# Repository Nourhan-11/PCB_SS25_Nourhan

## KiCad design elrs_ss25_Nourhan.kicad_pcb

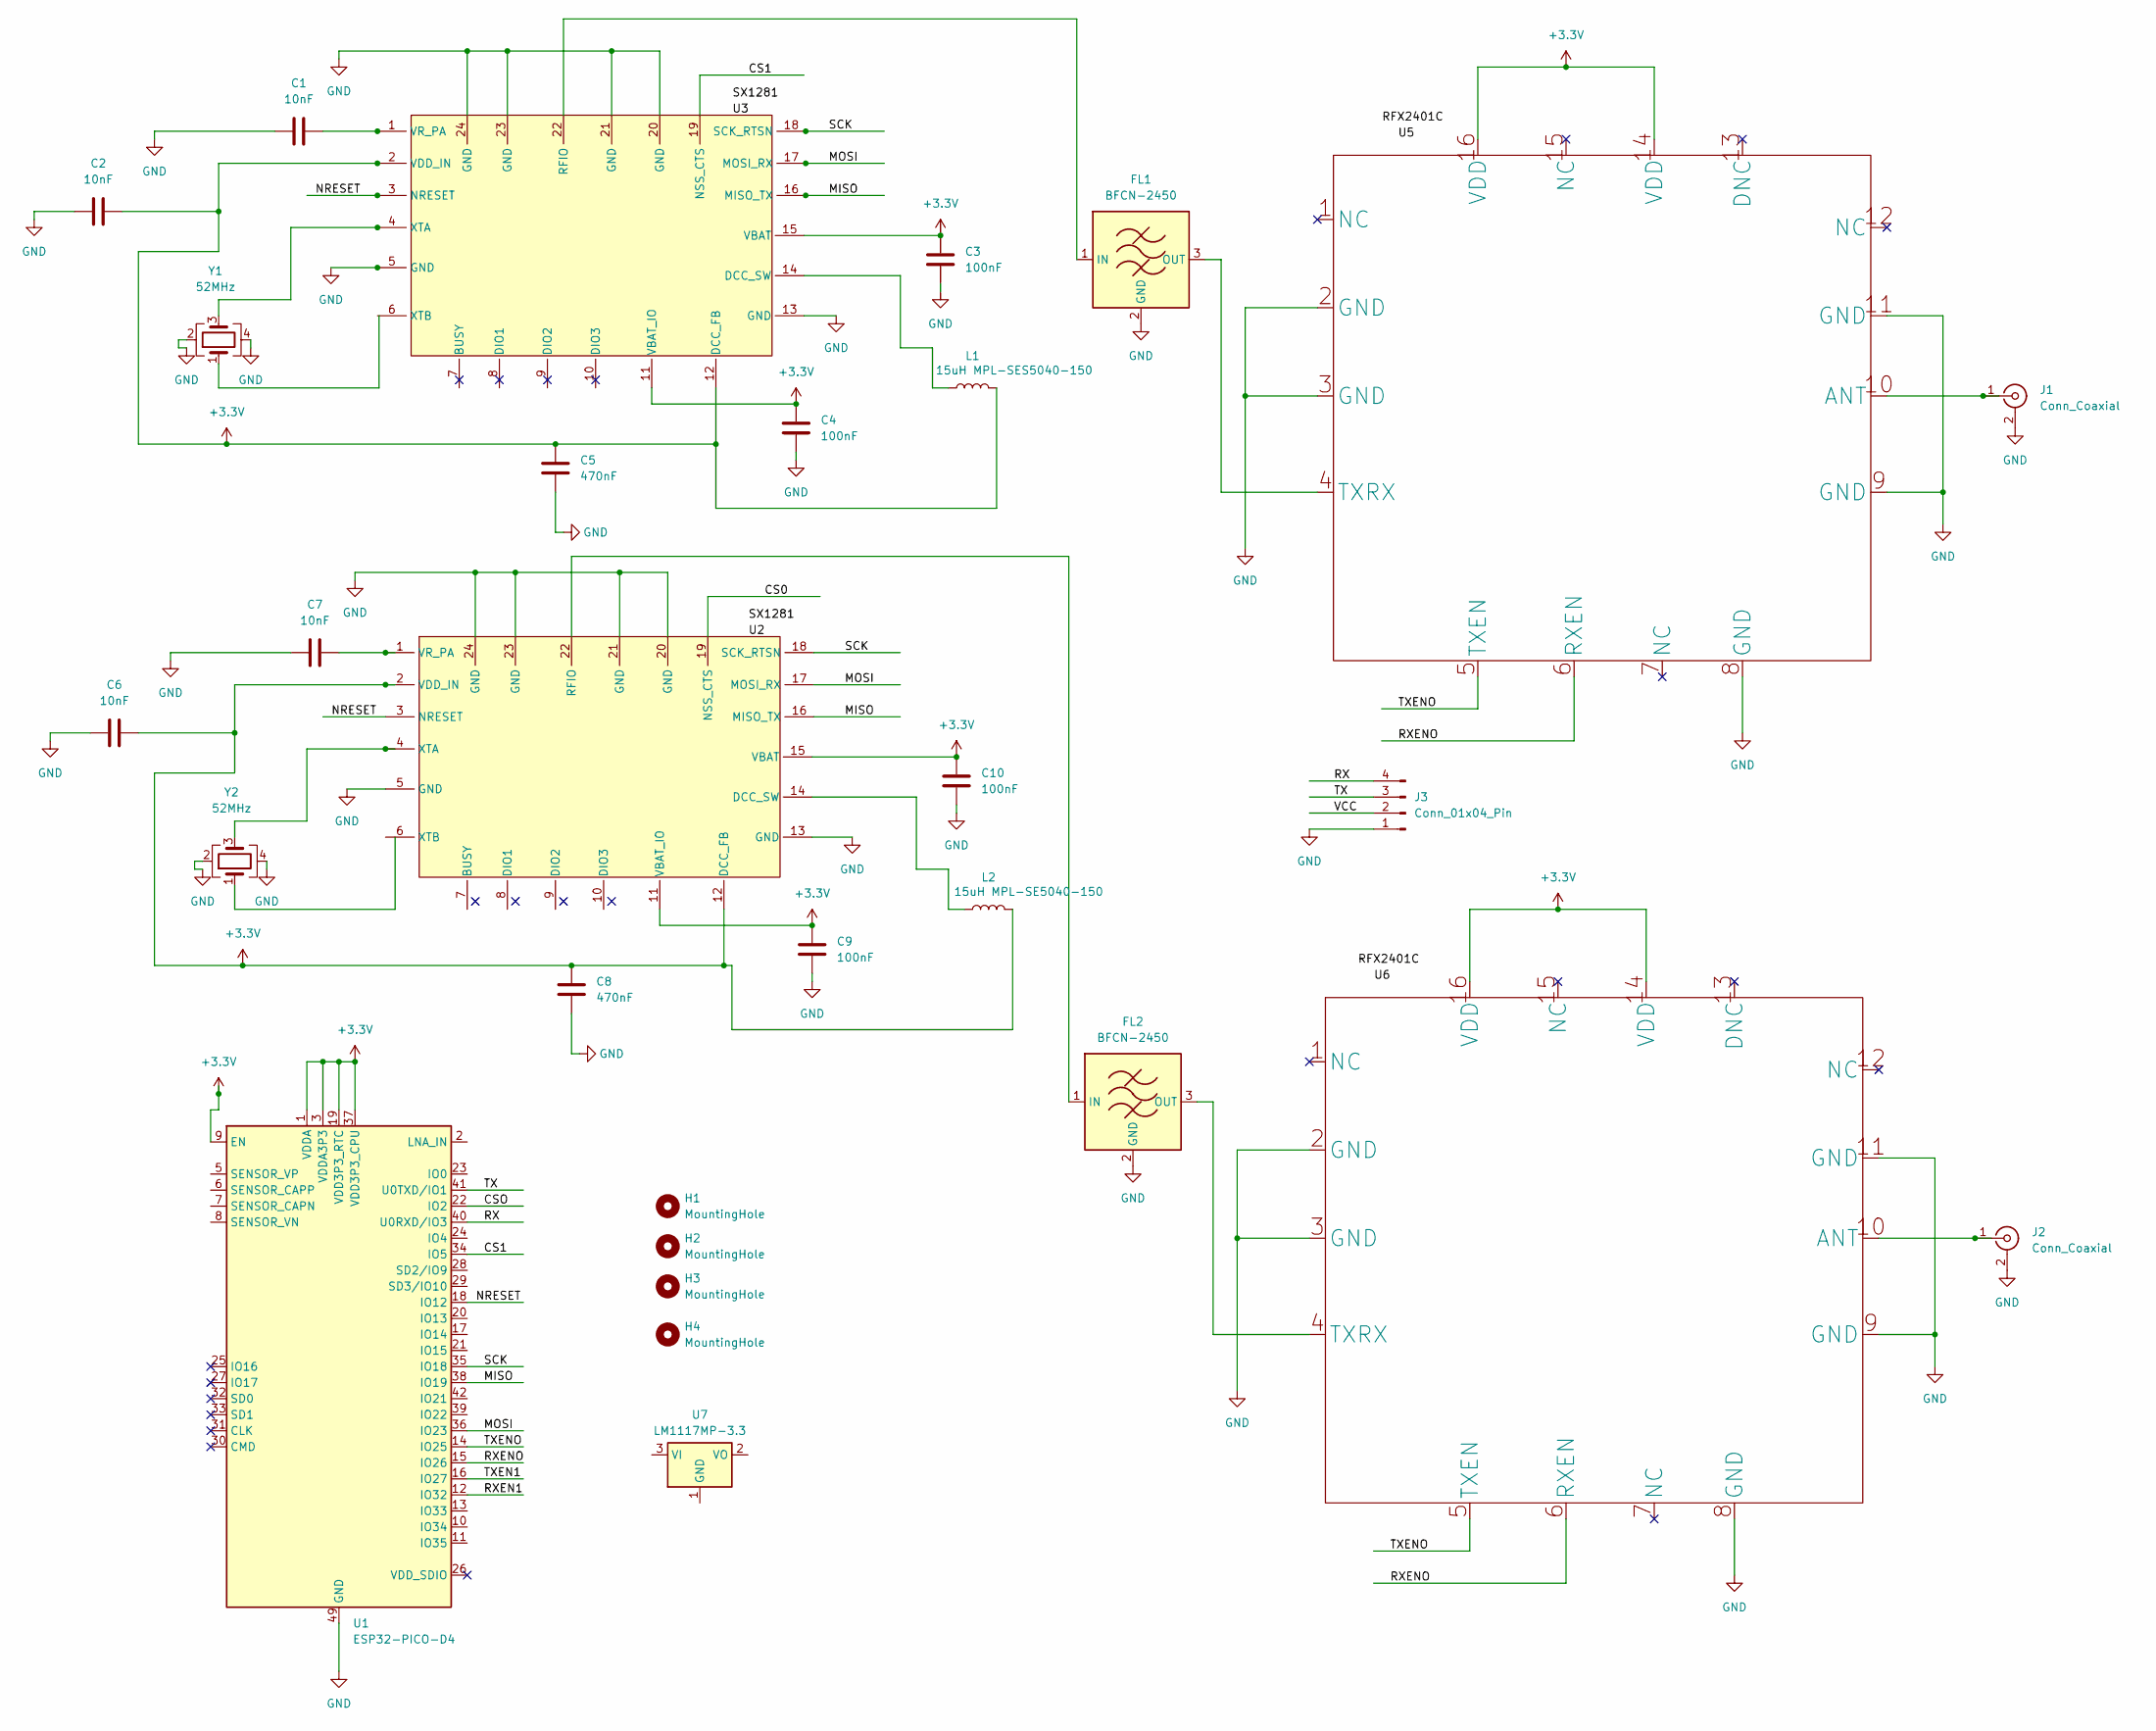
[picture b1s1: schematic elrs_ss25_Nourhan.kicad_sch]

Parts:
C1, C2, C6, C7: 10nF; C_0603_1608Metric_Pad1.08x0.95mm_HandSolder
C3, C4, C9, C10: 100nF; C_0603_1608Metric_Pad1.08x0.95mm_HandSolder
C5, C8: 470nF; C_0603_1608Metric_Pad1.08x0.95mm_HandSolder
FL1, FL2: BFCN-2450; Filter_Mini-Circuits_FV1206-4
H1, H2, H3, H4: MountingHole; MountingHole_3.2mm_M3
J1, J2: Conn_Coaxial; U.FL_Molex_MCRF_73412-0110_Vertical
J3: Conn_01x04_Pin; JST_GH_SM04B-GHS-TB_1x04-1MP_P1.25mm_Horizontal
L1: 15uH MPL-SES5040-150; L_APV_ANR5045
L2: 15uH MPL-SE5040-150; L_APV_ANR5045
U1: ESP32-PICO-D4; QFN-48-1EP_7x7mm_P0.5mm_EP5.3x5.3mm
U2, U3: QFN-24-1EP_4x4mm_P0.5mm_EP2.7x2.7mm
U4, U6: QFN-16-1EP_3x3mm_P0.5mm_EP1.75x1.75mm
U7: LM1117MP-3.3; SOT-223-3_TabPin2
Y1, Y2: 52MHz

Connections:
+3.3V: C2.2, C3.2, C4.2, C5.1, C6.2, C8.1, C9.2, C10.2, L1.2, L2.2, U1.1 (VDDA), U1.3 (VDDA3P3), U1.4 (VDDA3P3), U1.9 (EN), U1.19 (VDD3P3_RTC), U1.37 (VDD3P3_CPU), U1.43 (VDDA), U1.46 (VDDA), U2.2 (VDD_IN), U2.11 (VBAT_IO), U2.12 (DCC_FB), U2.15 (VBAT), U3.2 (VDD_IN), U3.11 (VBAT_IO), U3.12 (DCC_FB), U3.15 (VBAT), U4.14 (VDD), U4.16 (VDD), U6.14 (VDD), U6.16 (VDD); also elsewhere on the board
/CS0: U3.19 (NSS_CTS)
/CS1: U1.34 (IO5), U2.19 (NSS_CTS)
/CSO: U1.22 (IO2)
/MISO: U1.38 (IO19), U2.16 (MISO_TX), U3.16 (MISO_TX)
/MOSI: U1.36 (IO23), U2.17 (MOSI_RX), U3.17 (MOSI_RX)
/NRESET: U1.18 (IO12), U2.3 (NRESET), U3.3 (NRESET)
/RX: J3.4, U1.40 (U0RXD/IO3)
/RXEN1: U1.12 (IO32)
/RXENO: U1.15 (IO26), U4.6 (RXEN), U6.6 (RXEN)
/SCK: U1.35 (IO18), U2.18 (SCK_RTSN), U3.18 (SCK_RTSN)
/TX: J3.3, U1.41 (U0TXD/IO1)
/TXEN1: U1.16 (IO27)
/TXENO: U1.14 (IO25), U4.5 (TXEN), U6.5 (TXEN)
/VCC: J3.2; also elsewhere on the board
GND: C1.1, C2.1, C3.1, C4.1, C5.2, C6.1, C7.1, C8.2, C9.1, C10.1, FL1.2 (GND), FL1.4 (GND), FL2.2 (GND), FL2.4 (GND), J1.2 (Ext), J2.2 (Ext), J3.1, U1.49 (GND), U2.5 (GND), U2.13 (GND), U2.20 (GND), U2.21 (GND), U2.23 (GND), U2.24 (GND), U3.5 (GND), U3.13 (GND), U3.20 (GND), U3.21 (GND), U3.23 (GND), U3.24 (GND), U4.2 (GND), U4.3 (GND), U4.8 (GND), U4.9 (GND), U4.11 (GND), U6.2 (GND), U6.3 (GND), U6.8 (GND), U6.9 (GND), U6.11 (GND), Y1.2, Y1.4, Y2.2, Y2.4; also elsewhere on the board
unnamed: FL1.1 (IN), U2.22 (RFIO)
unnamed: FL1.3 (OUT), U4.4 (TXRX)
unnamed: FL2.1 (IN), U3.22 (RFIO)
unnamed: FL2.3 (OUT), U6.4 (TXRX)
unnamed: J1.1 (In), U4.10 (ANT)
unnamed: J2.1 (In), U6.10 (ANT)
unnamed: L1.1, U2.14 (DCC_SW)
unnamed: C1.2, U2.1 (VR_PA)
unnamed: U2.4 (XTA), Y1.3
unnamed: L2.1, U3.14 (DCC_SW)
unnamed: C7.2, U3.1 (VR_PA)
unnamed: U3.4 (XTA), Y2.3

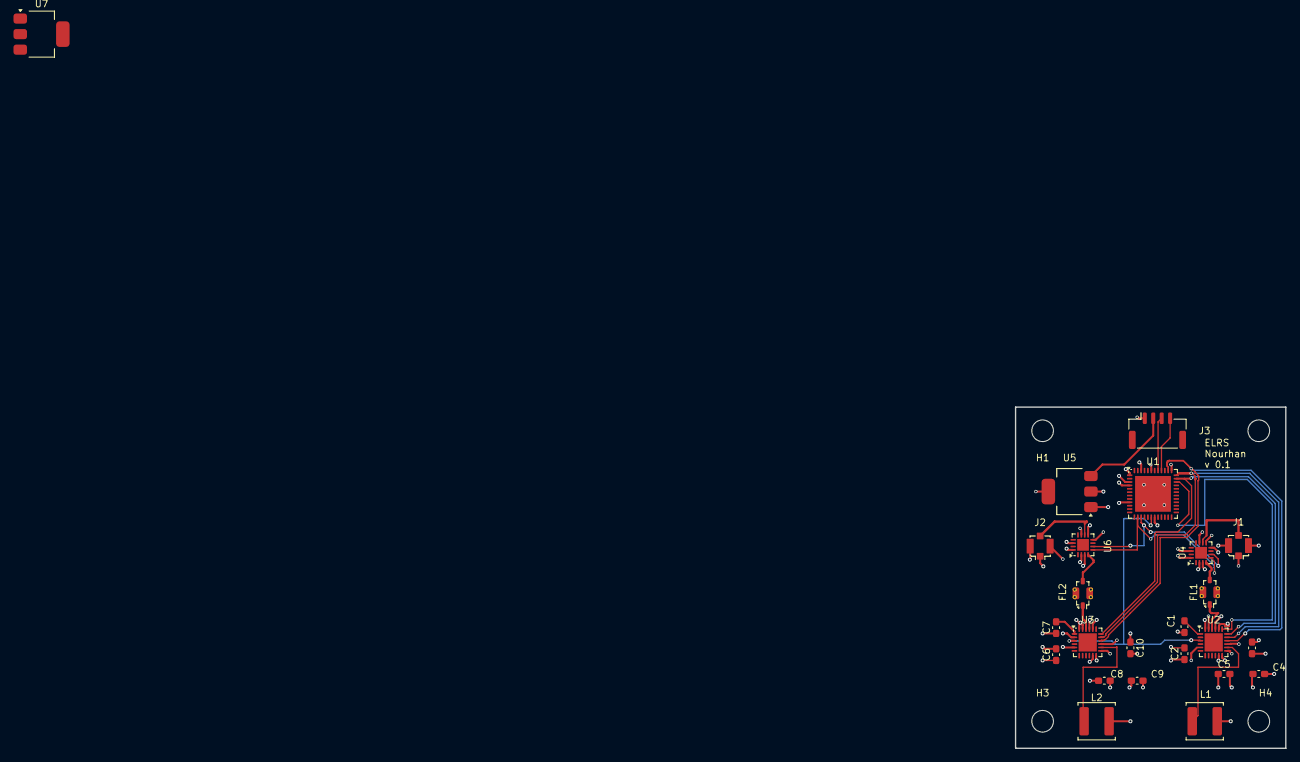
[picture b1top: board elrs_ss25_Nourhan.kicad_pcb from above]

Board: 4 copper layers, 40.0 x 50.5 mm, 28 parts (0 on the bottom side), 22 nets.

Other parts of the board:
U5: LM1117MP-3.3; SOT-223-3_TabPin2

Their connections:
+3.3V: U5.2 (VO); also elsewhere on the board
/VCC: U5.3 (VI); also elsewhere on the board
GND: U5.1 (GND); also elsewhere on the board

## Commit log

2025-06-11 Create Beispiel
